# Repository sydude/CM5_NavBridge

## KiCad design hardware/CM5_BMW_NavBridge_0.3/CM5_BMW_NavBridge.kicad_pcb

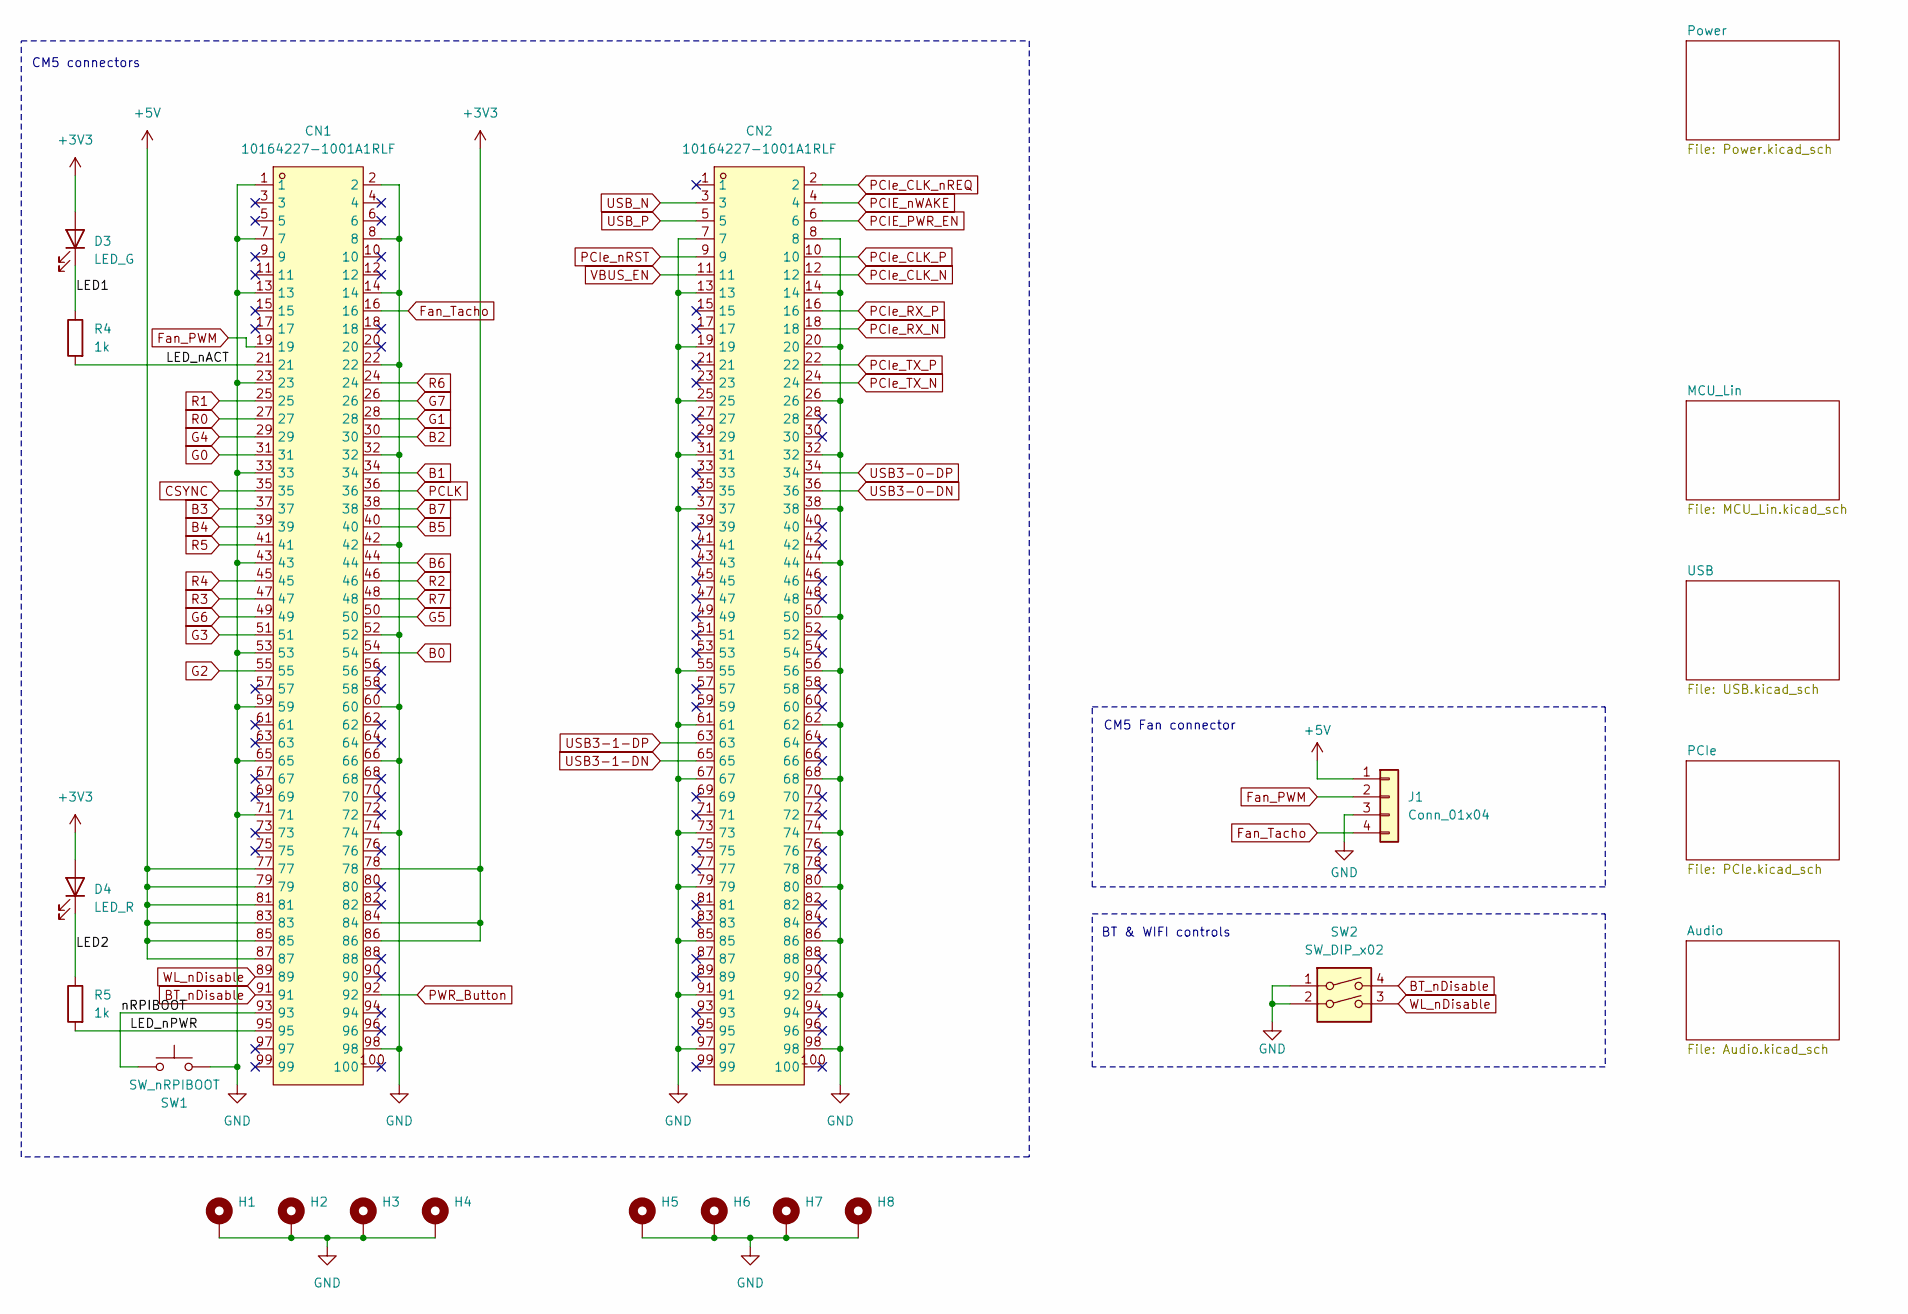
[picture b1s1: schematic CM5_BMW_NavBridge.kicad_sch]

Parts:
CN1, CN2: 10164227-1001A1RLF; CONN-SMD_100P-P0.40_10164227-1001A1RLF; MPN 10164227-1001A1RLF; LCSC Part C6782225
D3: LED_G; LED_0603_1608Metric_Pad1.05x0.95mm_HandSolder
D4: LED_R; LED_0603_1608Metric_Pad1.05x0.95mm_HandSolder
H1, H2, H3, H4, H5, H6, H7, H8: MountingHole_Pad; MountingHole_2.7mm_M2.5_Pad_TopBottom
J1: Conn_01x04; JST_SH_BM04B-SRSS-TB_1x04-1MP_P1.00mm_Vertical
R4, R5: 1k; R_0603_1608Metric_Pad0.98x0.95mm_HandSolder
SW1: SW_nRPIBOOT; SW_SPST_TS-1088-xR025; MPN TS-1088-AR02016; LCSC C720477
SW2: SW_DIP_x02; SW_DIP_SPSTx02_Slide_Copal_CHS-02B_W7.62mm_P1.27mm

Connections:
+3V3: CN1.78, CN1.84, CN1.86, D3.2 (A), D4.2 (A); also elsewhere on the board
+5V: CN1.77, CN1.79, CN1.81, CN1.83, CN1.85, CN1.87, J1.1; also elsewhere on the board
/LED1: D3.1 (K), R4.1
/LED2: D4.1 (K), R5.1
/LED_nACT: CN1.21, R4.2
/LED_nPWR: CN1.95, R5.2
/nRPIBOOT: CN1.93, SW1.1
B0: CN1.54
B1: CN1.34
B2: CN1.30
B3: CN1.37
B4: CN1.39
B5: CN1.40
B6: CN1.44
B7: CN1.38
BT_nDisable: CN1.91, SW2.4
CSYNC: CN1.35
Fan_PWM: CN1.19, J1.2
Fan_Tacho: CN1.16, J1.4
G0: CN1.31
G1: CN1.28
G2: CN1.55
G3: CN1.51
G4: CN1.29
G5: CN1.50
G6: CN1.49
G7: CN1.26
GND: CN1.1, CN1.2, CN1.7, CN1.8, CN1.13, CN1.14, CN1.22, CN1.23, CN1.32, CN1.33, CN1.42, CN1.43, CN1.52, CN1.53, CN1.59, CN1.60, CN1.65, CN1.66, CN1.71, CN1.74, CN1.98, CN2.7, CN2.8, CN2.13, CN2.14, CN2.19, CN2.20, CN2.25, CN2.26, CN2.31, CN2.32, CN2.37, CN2.38, CN2.44, CN2.50, CN2.55, CN2.56, CN2.61, CN2.62, CN2.67, CN2.68, CN2.73, CN2.74, CN2.79, CN2.80, CN2.85, CN2.86, CN2.91, CN2.92, CN2.97, CN2.98, H1.1 (1_1), H2.1 (1_1), H3.1 (1_1), H4.1 (1_1), H5.1 (1_1), H6.1 (1_1), H7.1 (1_1), H8.1 (1_1), J1.3, SW1.2, SW2.1, SW2.2; also elsewhere on the board
PCIE_PWR_EN: CN2.6; also elsewhere on the board
PCIE_nWAKE: CN2.4; also elsewhere on the board
PCIe_CLK_N: CN2.12; also elsewhere on the board
PCIe_CLK_P: CN2.10; also elsewhere on the board
PCIe_CLK_nREQ: CN2.2; also elsewhere on the board
PCIe_RX_N: CN2.18; also elsewhere on the board
PCIe_RX_P: CN2.16; also elsewhere on the board
PCIe_TX_N: CN2.24; also elsewhere on the board
PCIe_TX_P: CN2.22; also elsewhere on the board
PCIe_nRST: CN2.9; also elsewhere on the board
PCLK: CN1.36
PWR_Button: CN1.92; also elsewhere on the board
R0: CN1.27
R1: CN1.25
R2: CN1.46
R3: CN1.47
R4: CN1.45
R5: CN1.41
R6: CN1.24
R7: CN1.48
USB3-0-DN: CN2.36; also elsewhere on the board
USB3-0-DP: CN2.34; also elsewhere on the board
USB3-1-DN: CN2.65; also elsewhere on the board
USB3-1-DP: CN2.63; also elsewhere on the board
USB_N: CN2.3; also elsewhere on the board
USB_P: CN2.5; also elsewhere on the board
VBUS_EN: CN2.11; also elsewhere on the board
WL_nDisable: CN1.89, SW2.3

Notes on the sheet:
CM5 Fan connector
CM5 connectors
BT & WIFI controls

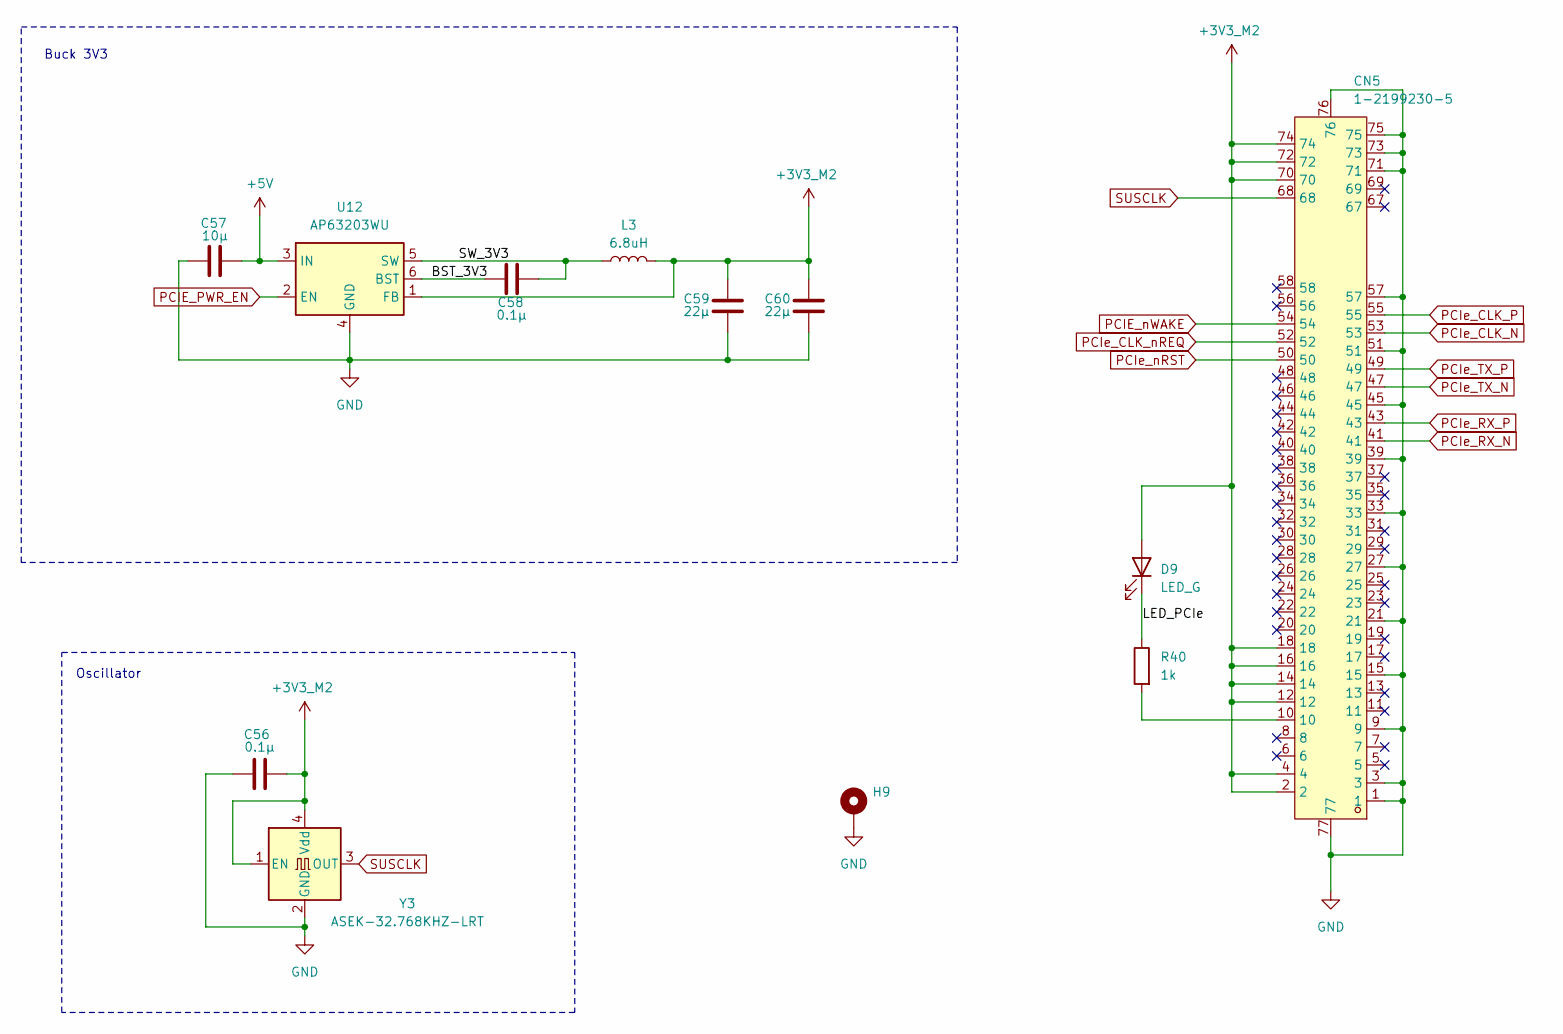
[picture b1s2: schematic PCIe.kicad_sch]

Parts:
C56, C58: 0.1µ; C_0603_1608Metric_Pad1.08x0.95mm_HandSolder; LCSC C1591
C57: 10µ; C_0805_2012Metric_Pad1.18x1.45mm_HandSolder; LCSC C95841
C59, C60: 22µ; C_1206_3216Metric_Pad1.33x1.80mm_HandSolder; LCSC C87996
CN5: 1-2199230-5; PCIE-SMD_75P-P0.50_1-2199230-5; LCSC Part C590854
D9: LED_G; LED_0603_1608Metric_Pad1.05x0.95mm_HandSolder
H9: MountingHole_Pad; MountingHole_2.2mm_M2_DIN965_Pad_TopBottom
L3: 6.8uH; L_Sunlord_MWSA0518S; LCSC C2928918
R40: 1k; R_0603_1608Metric_Pad0.98x0.95mm_HandSolder
U12: AP63203WU; TSOT-23-6; LCSC C780769
Y3: ASEK-32.768KHZ-LRT; Oscillator_SMD_Abracon_ASE-4Pin_3.2x2.5mm_HandSoldering; LCSC C2650753

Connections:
+3V3_M2: C56.1, C59.1, C60.1, CN5.2, CN5.4, CN5.12, CN5.14, CN5.16, CN5.18, CN5.70, CN5.72, CN5.74, D9.2 (A), L3.2, U12.1 (FB), Y3.1 (EN), Y3.4 (Vdd)
+5V: C57.2, U12.3 (IN); also elsewhere on the board
/PCIe/BST_3V3: C58.2, U12.6 (BST)
/PCIe/LED_PCIe: D9.1 (K), R40.1
/PCIe/SW_3V3: C58.1, L3.1, U12.5 (SW)
GND: C56.2, C57.1, C59.2, C60.2, CN5.1, CN5.3, CN5.9, CN5.15, CN5.21, CN5.27, CN5.33, CN5.39, CN5.45, CN5.51, CN5.57, CN5.71, CN5.73, CN5.75, CN5.76, CN5.77, H9.1 (1_1), U12.4 (GND), Y3.2 (GND); also elsewhere on the board
unnamed: CN5.10, R40.2
PCIE_PWR_EN: U12.2 (EN); also elsewhere on the board
PCIE_nWAKE: CN5.54; also elsewhere on the board
PCIe_CLK_N: CN5.53; also elsewhere on the board
PCIe_CLK_P: CN5.55; also elsewhere on the board
PCIe_CLK_nREQ: CN5.52; also elsewhere on the board
PCIe_RX_N: CN5.41; also elsewhere on the board
PCIe_RX_P: CN5.43; also elsewhere on the board
PCIe_TX_N: CN5.47; also elsewhere on the board
PCIe_TX_P: CN5.49; also elsewhere on the board
PCIe_nRST: CN5.50; also elsewhere on the board
SUSCLK: CN5.68, Y3.3 (OUT)

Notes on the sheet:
Buck 3V3
Oscillator

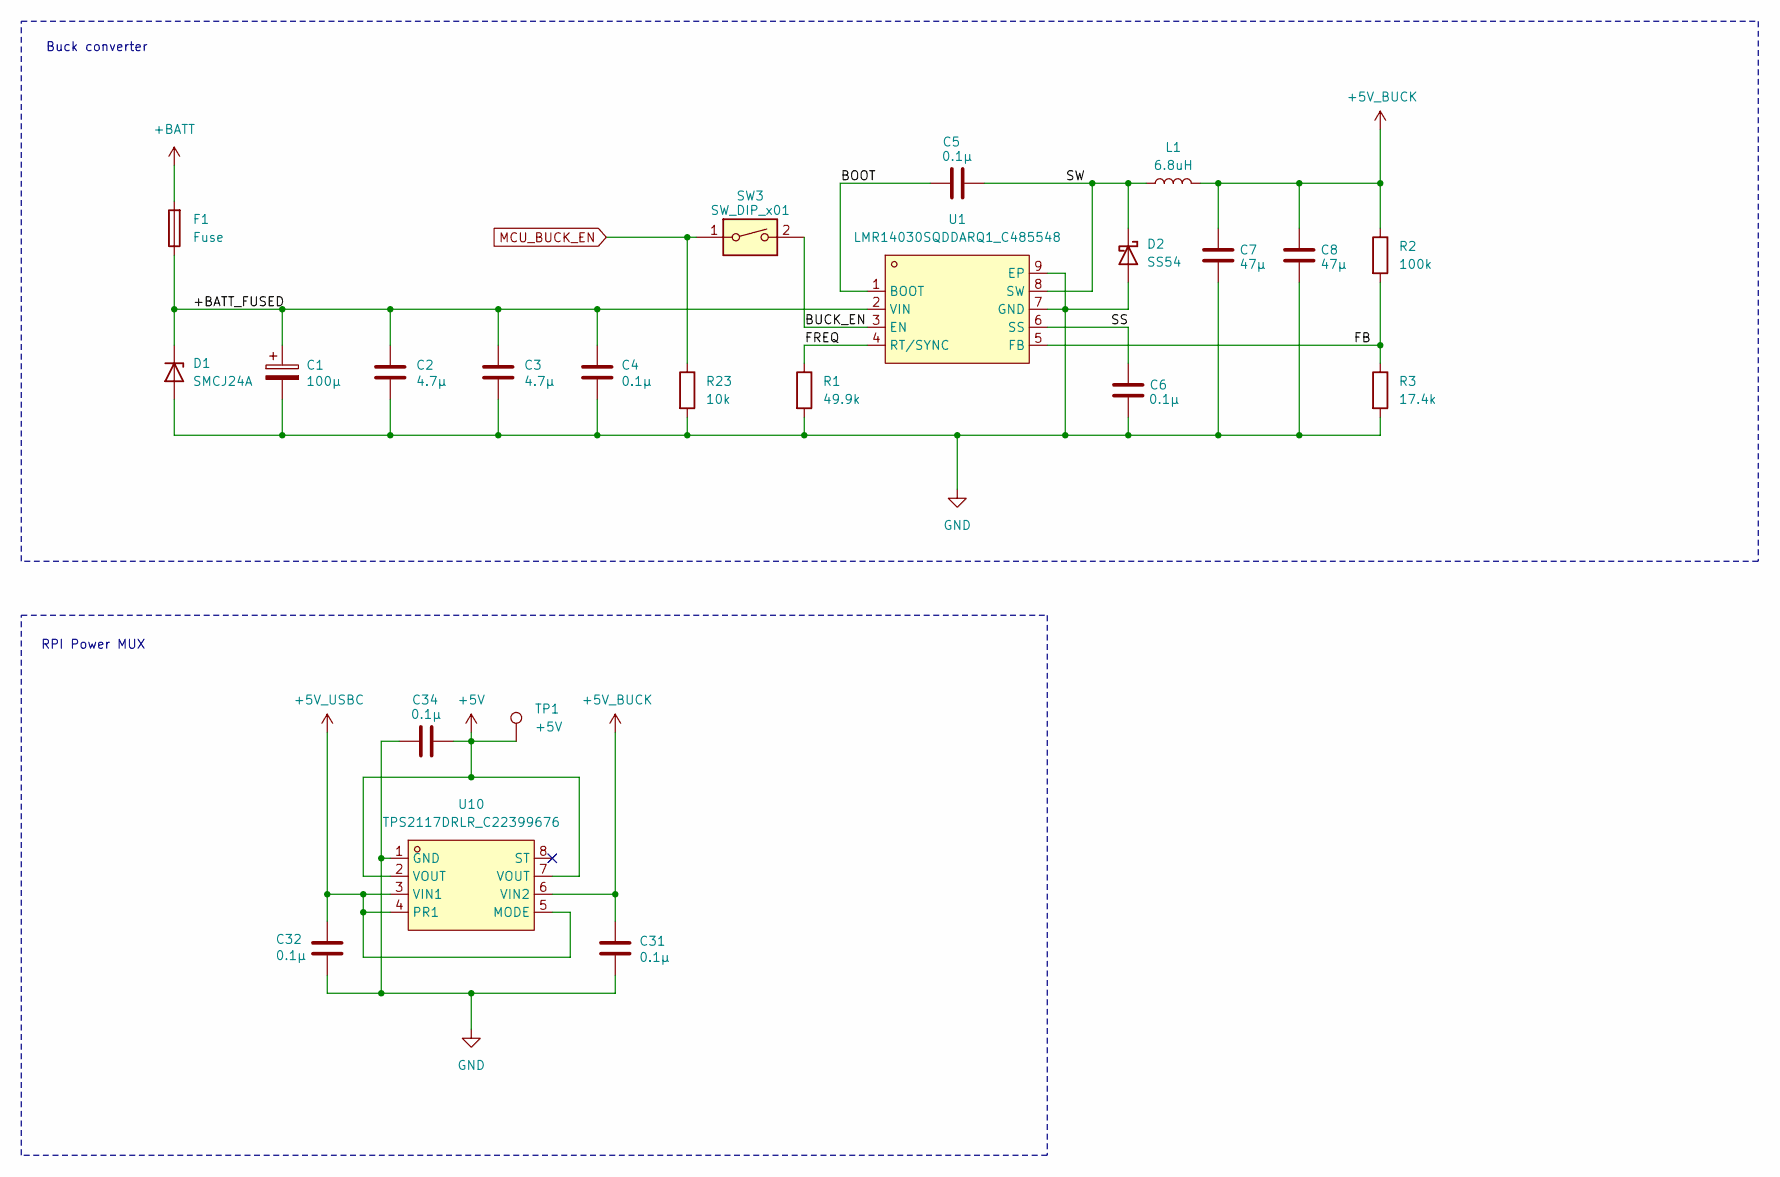
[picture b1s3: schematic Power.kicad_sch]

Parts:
C1: 100µ; CP_Elec_6.3x5.8; LCSC C128464
C2, C3: 4.7µ; C_1206_3216Metric_Pad1.33x1.80mm_HandSolder; LCSC C51205
C4, C5, C6, C31, C32, C34: 0.1µ; C_0603_1608Metric_Pad1.08x0.95mm_HandSolder; LCSC C1591
C7, C8: 47µ; C_1210_3225Metric_Pad1.33x2.70mm_HandSolder; LCSC C2932477
D1: SMCJ24A; D_SMC; LCSC C224045
D2: SS54; D_SMA; LCSC C22452
F1: Fuse; Fuseholder_Littelfuse_Nano2_154x; LCSC C108518
L1: 6.8uH; L_Sunlord_MWSA1003S; LCSC C2453947
R1: 49.9k; R_0603_1608Metric_Pad0.98x0.95mm_HandSolder
R2: 100k; R_0603_1608Metric_Pad0.98x0.95mm_HandSolder
R3: 17.4k; R_0603_1608Metric_Pad0.98x0.95mm_HandSolder
R23: 10k; R_0603_1608Metric_Pad0.98x0.95mm_HandSolder
SW3: SW_DIP_x01; SW_DIP_SPSTx01_Slide_Copal_CHS-01B_W7.62mm_P1.27mm
TP1: +5V; TestPoint_Pad_1.0x1.0mm
U1: LMR14030SQDDARQ1_C485548; SOPOWERPAD-8_L4.9-W3.9-P1.27-LS6.0-BL-EP; LCSC Part C485548
U10: TPS2117DRLR_C22399676; SOT-583-8_L2.1-W1.2-P0.50-LS1.6-BL; LCSC Part C22399676

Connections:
+5V: C34.2, TP1.1 (1_1), U10.2 (VOUT), U10.7 (VOUT); also elsewhere on the board
+5V_BUCK: C7.1, C8.1, C31.1, L1.2, R2.1, U10.6 (VIN2); also elsewhere on the board
+5V_USBC: C32.1, U10.3 (VIN1), U10.4 (PR1), U10.5 (MODE); also elsewhere on the board
+BATT: F1.2
/Power/+BATT_FUSED: C1.1, C2.1, C3.1, C4.1, D1.1 (K), F1.1, U1.2 (VIN)
/Power/BOOT: C5.1, U1.1 (BOOT)
/Power/BUCK_EN: SW3.2, U1.3 (EN)
/Power/FB: R2.2, R3.1, U1.5 (FB)
/Power/FREQ: R1.1, U1.4 (RT/SYNC)
/Power/SS: C6.1, U1.6 (SS)
/Power/SW: C5.2, D2.1 (K), L1.1, U1.8 (SW)
GND: C1.2, C2.2, C3.2, C4.2, C6.2, C7.2, C8.2, C31.2, C32.2, C34.1, D1.2 (A), D2.2 (A), R1.2, R3.2, R23.2, U1.7 (GND), U1.9 (EP), U10.1 (GND); also elsewhere on the board
MCU_BUCK_EN: R23.1, SW3.1; also elsewhere on the board

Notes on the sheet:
Buck converter
RPI Power MUX

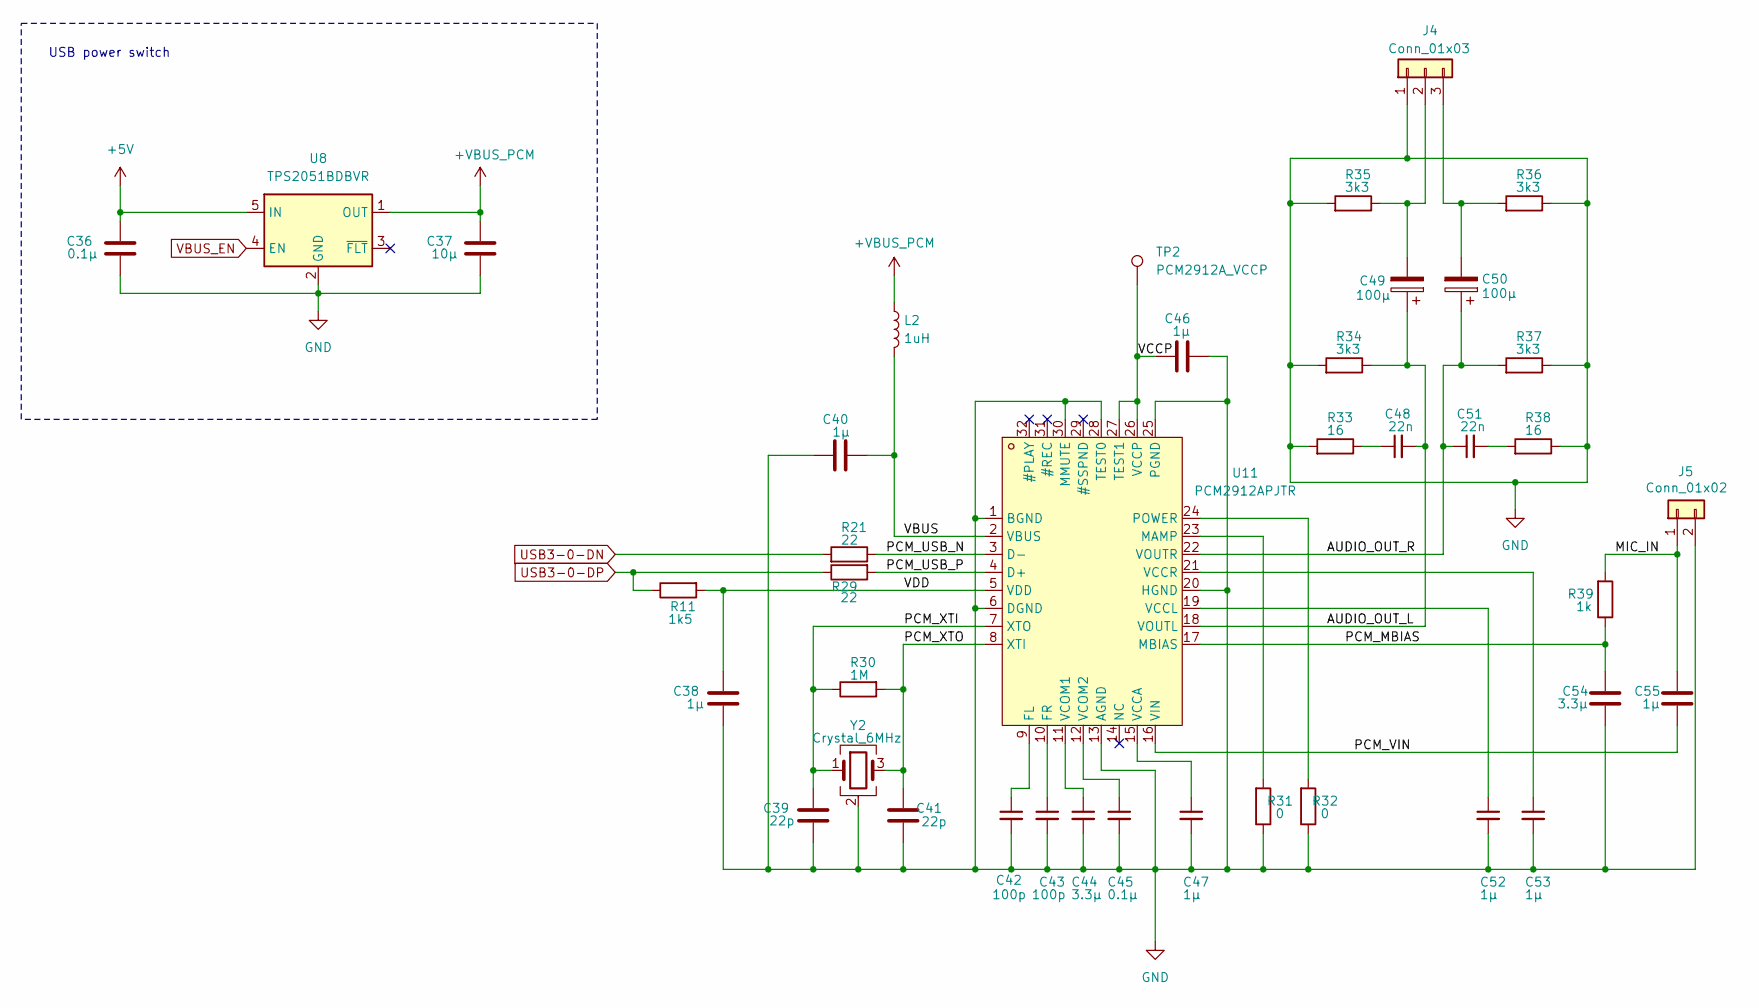
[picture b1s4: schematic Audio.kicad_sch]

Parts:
C36, C45: 0.1µ; C_0603_1608Metric_Pad1.08x0.95mm_HandSolder; LCSC C1591
C37: 10µ; C_0805_2012Metric_Pad1.18x1.45mm_HandSolder; LCSC C95841
C38, C40, C46, C47, C52, C53, C55: 1µ; C_0603_1608Metric_Pad1.08x0.95mm_HandSolder; LCSC C29936
C39, C41: 22p; C_0603_1608Metric_Pad1.08x0.95mm_HandSolder; LCSC C1653
C42, C43: 100p; C_0603_1608Metric_Pad1.08x0.95mm_HandSolder; LCSC C14858
C44, C54: 3.3µ; C_0603_1608Metric_Pad1.08x0.95mm_HandSolder; LCSC C51412
C48, C51: 22n; C_0603_1608Metric_Pad1.08x0.95mm_HandSolder; LCSC C21122
C49, C50: 100µ; CP_EIA-3528-21_Kemet-B_HandSolder; LCSC C79109
J4: Conn_01x03; JST_GH_SM03B-GHS-TB_1x03-1MP_P1.25mm_Horizontal
J5: Conn_01x02; JST_GH_SM02B-GHS-TB_1x02-1MP_P1.25mm_Horizontal
L2: 1uH; L_1008_2520Metric_Pad1.43x2.20mm_HandSolder; LCSC C435392
R11: 1k5; R_0603_1608Metric_Pad0.98x0.95mm_HandSolder
R21, R29: 22; R_0603_1608Metric_Pad0.98x0.95mm_HandSolder
R30: 1M; R_0603_1608Metric_Pad0.98x0.95mm_HandSolder
R31, R32: 0; R_0603_1608Metric_Pad0.98x0.95mm_HandSolder
R33, R38: 16; R_0603_1608Metric_Pad0.98x0.95mm_HandSolder
R34, R35, R36, R37: 3k3; R_0603_1608Metric_Pad0.98x0.95mm_HandSolder
R39: 1k; R_0603_1608Metric_Pad0.98x0.95mm_HandSolder
TP2: PCM2912A_VCCP; TestPoint_Pad_1.0x1.0mm
U8: TPS2051BDBVR; SOT-23-5; LCSC C24593
U11: PCM2912APJTR; TQFP-32_L7.0-W7.0-P0.80-LS9.0-TL; MPN PCM2912APJTR; LCSC Part C475497
Y2: Crystal_6MHz; Crystal_SMD_FOX_FQ7050-4Pin_7.0x5.0mm; MPN ABMM-6.000MHZ-B2-T; LCSC C179631

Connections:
+5V: C36.2, U8.5 (IN); also elsewhere on the board
+VBUS_PCM: C37.2, L2.1, U8.1 (OUT)
/Audio/AUDIO_OUT_L: C48.2, C49.1, R34.1, U11.18 (VOUTL)
/Audio/AUDIO_OUT_R: C50.1, C51.1, R37.2, U11.22 (VOUTR)
/Audio/MIC_IN: C55.1, J5.1, R39.2
/Audio/PCM_MBIAS: C54.1, R39.1, U11.17 (MBIAS)
/Audio/PCM_USB_N: R21.1, U11.3 (D-)
/Audio/PCM_USB_P: R29.2, U11.4 (D+)
/Audio/PCM_VIN: C55.2, U11.16 (VIN)
/Audio/PCM_XTI: C39.2, R30.1, U11.7 (XTO), Y2.1
/Audio/PCM_XTO: C41.2, R30.2, U11.8 (XTI), Y2.3
/Audio/VBUS: C40.1, L2.2, U11.2 (VBUS)
/Audio/VCCP: C46.1, TP2.1 (1_1), U11.26 (VCCP), U11.27 (TEST1)
/Audio/VDD: C38.2, R11.2, U11.5 (VDD)
GND: C36.1, C37.1, C38.1, C39.1, C40.2, C41.1, C42.2, C43.2, C44.2, C45.2, C46.2, C47.2, C52.2, C53.2, C54.2, J4.1, J5.2, R31.1, R32.1, R33.2, R34.2, R35.2, R36.1, R37.1, R38.1, U8.2 (GND), U11.1 (BGND), U11.6 (DGND), U11.13 (AGND), U11.20 (HGND), U11.25 (PGND), U11.28 (TEST0), U11.30 (MMUTE), Y2.2 (G), Y2.4 (G); also elsewhere on the board
unnamed: C48.1, R33.1
unnamed: C51.2, R38.2
unnamed: C49.2, J4.2, R35.1
unnamed: C50.2, J4.3, R36.2
unnamed: C42.1, U11.9 (FL)
unnamed: C43.1, U11.10 (FR)
unnamed: R31.2, U11.23 (MAMP)
unnamed: R32.2, U11.24 (POWER)
unnamed: C47.1, U11.15 (VCCA)
unnamed: C52.1, U11.19 (VCCL)
unnamed: C53.1, U11.21 (VCCR)
unnamed: C44.1, U11.11 (VCOM1)
unnamed: C45.1, U11.12 (VCOM2)
USB3-0-DN: R21.2; also elsewhere on the board
USB3-0-DP: R11.1, R29.1; also elsewhere on the board
VBUS_EN: U8.4 (EN); also elsewhere on the board

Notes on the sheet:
USB power switch

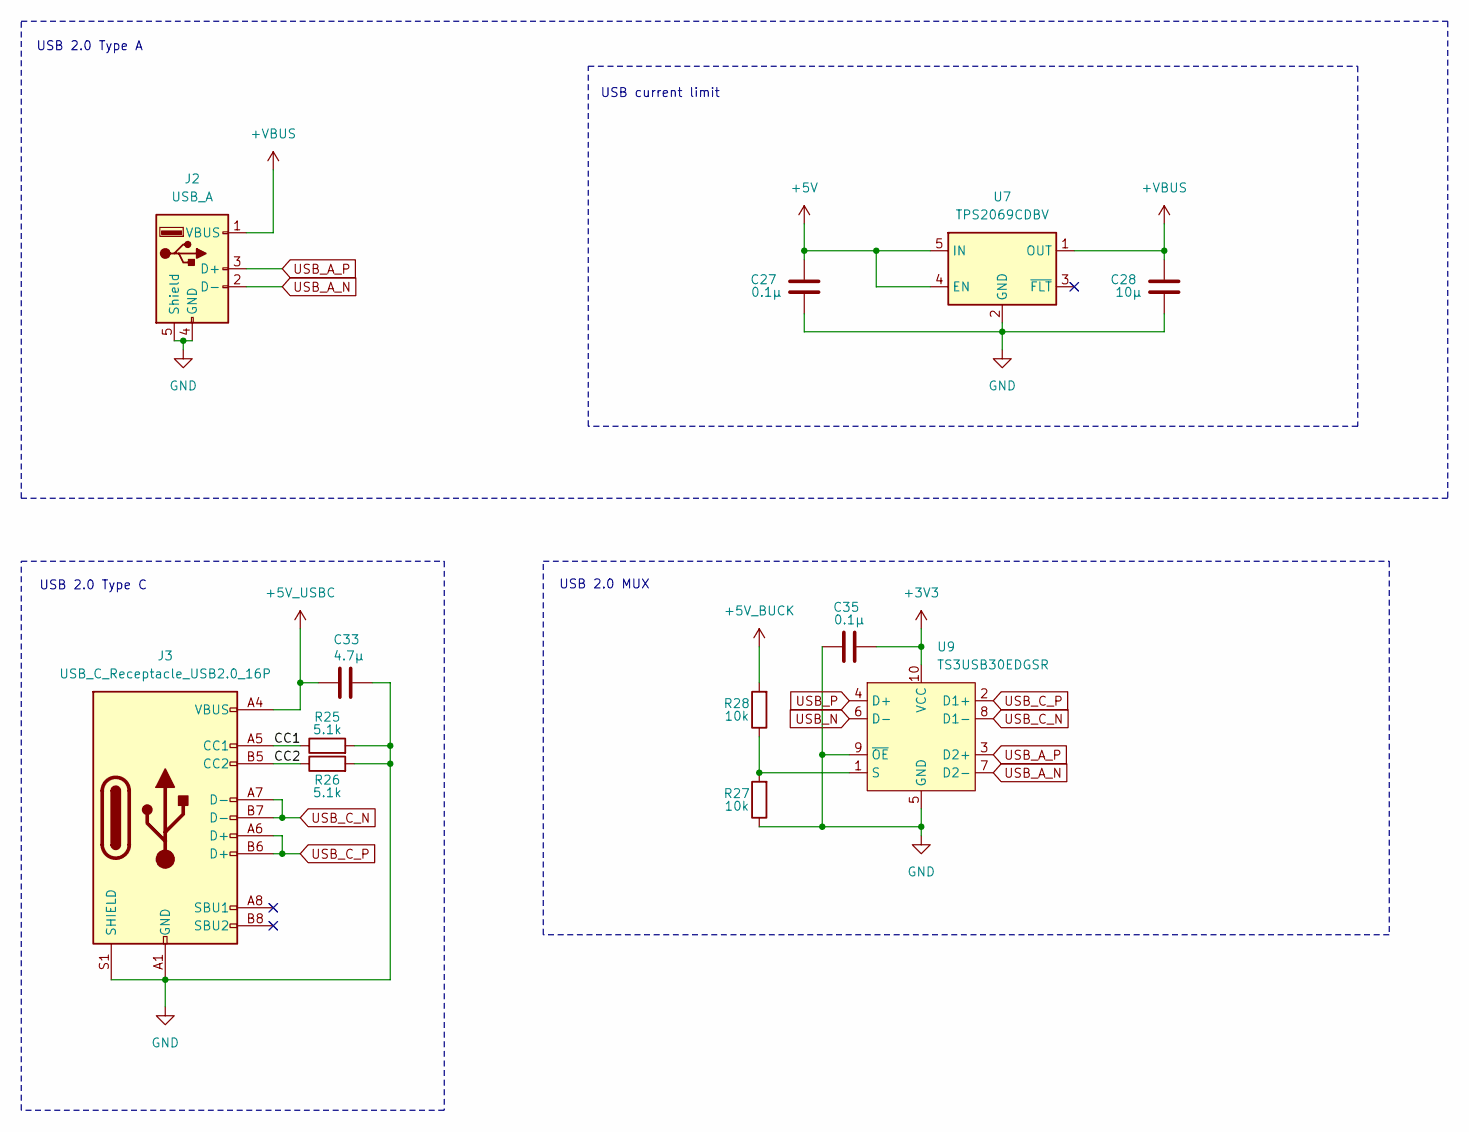
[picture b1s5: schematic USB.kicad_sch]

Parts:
C27, C35: 0.1µ; C_0603_1608Metric_Pad1.08x0.95mm_HandSolder; LCSC C1591
C28: 10µ; C_0805_2012Metric_Pad1.18x1.45mm_HandSolder; LCSC C95841
C33: 4.7µ; C_1206_3216Metric_Pad1.33x1.80mm_HandSolder; LCSC C51205
J2: USB_A; USB_A_Receptacle_GCT_USB1046
J3: USB_C_Receptacle_USB2.0_16P; USB_C_Receptacle_G-Switch_GT-USB-7010ASV; LCSC C2988369
R25, R26: 5.1k; R_0603_1608Metric_Pad0.98x0.95mm_HandSolder
R27, R28: 10k; R_0603_1608Metric_Pad0.98x0.95mm_HandSolder
U7: TPS2069CDBV; SOT-23-5; MPN TPS2069CDBVR
U9: TS3USB30EDGSR; VSSOP-10_3x3mm_P0.5mm

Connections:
+3V3: C35.1, U9.10 (VCC); also elsewhere on the board
+5V: C27.2, U7.4 (EN), U7.5 (IN); also elsewhere on the board
+5V_BUCK: R28.2; also elsewhere on the board
+5V_USBC: C33.1, J3.A4 (VBUS), J3.A9 (VBUS), J3.B4 (VBUS), J3.B9 (VBUS); also elsewhere on the board
+VBUS: C28.2, J2.1 (VBUS), U7.1 (OUT)
/USB/CC1: J3.A5 (CC1), R25.1
/USB/CC2: J3.B5 (CC2), R26.1
GND: C27.1, C28.1, C33.2, C35.2, J2.4 (GND), J2.5 (Shield), J3.A1 (GND), J3.A12 (GND), J3.B1 (GND), J3.B12 (GND), J3.S1 (SHIELD), R25.2, R26.2, R27.1, U7.2 (GND), U9.5 (GND), U9.9 (~OE); also elsewhere on the board
unnamed: R27.2, R28.1, U9.1 (S)
USB_A_N: J2.2 (D-), U9.7 (D2-)
USB_A_P: J2.3 (D+), U9.3 (D2+)
USB_C_N: J3.A7 (D-), J3.B7 (D-), U9.8 (D1-)
USB_C_P: J3.A6 (D+), J3.B6 (D+), U9.2 (D1+)
USB_N: U9.6 (D-); also elsewhere on the board
USB_P: U9.4 (D+); also elsewhere on the board

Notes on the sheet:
USB current limit
USB 2.0 Type A
USB 2.0 MUX
USB 2.0 Type C

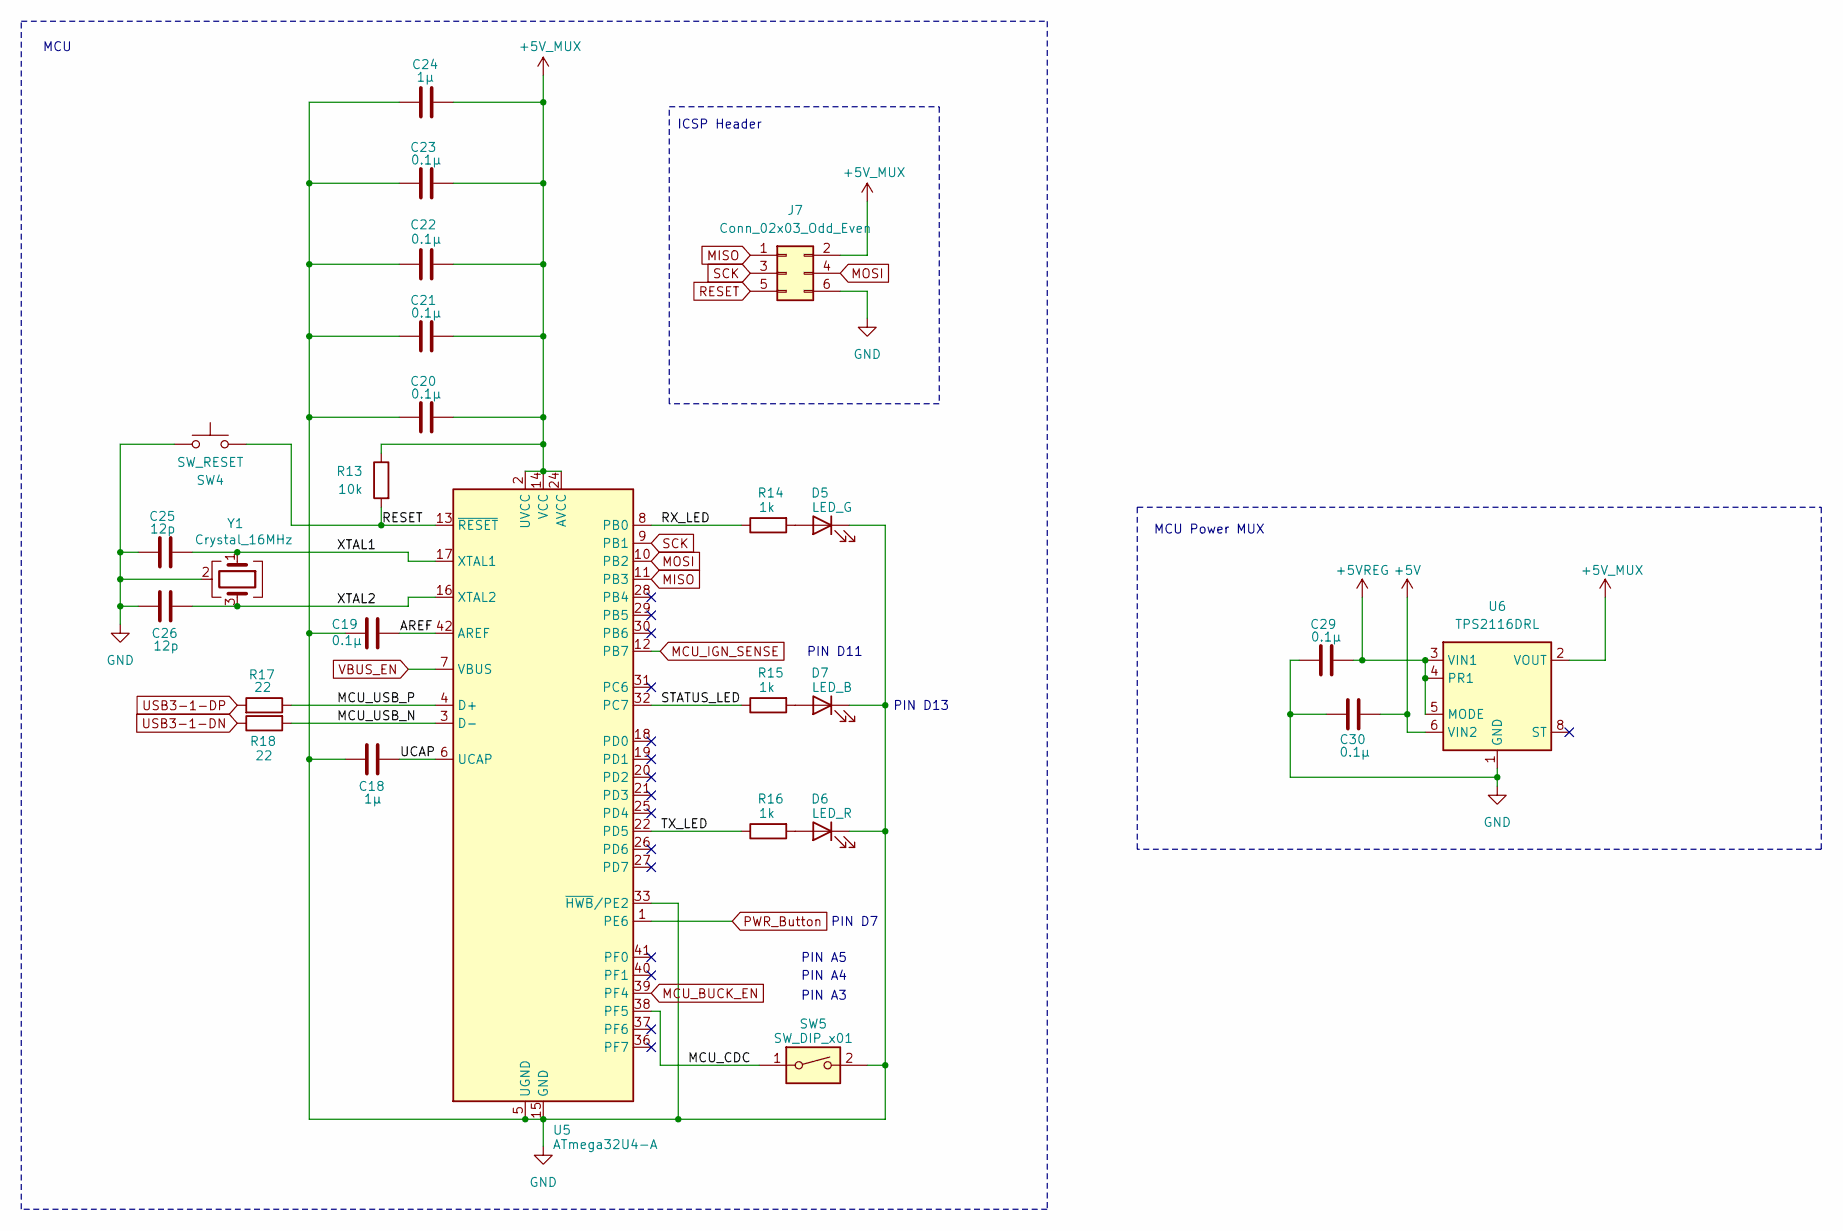
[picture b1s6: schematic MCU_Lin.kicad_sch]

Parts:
C18, C24: 1µ; C_0603_1608Metric_Pad1.08x0.95mm_HandSolder; LCSC C1591
C19, C20, C21, C22, C23, C29, C30: 0.1µ; C_0603_1608Metric_Pad1.08x0.95mm_HandSolder; LCSC C1591
C25, C26: 12p; C_0603_1608Metric_Pad1.08x0.95mm_HandSolder; LCSC C38523
D5: LED_G; LED_0603_1608Metric_Pad1.05x0.95mm_HandSolder
D6: LED_R; LED_0603_1608Metric_Pad1.05x0.95mm_HandSolder
D7: LED_B; LED_0603_1608Metric_Pad1.05x0.95mm_HandSolder
J7: Conn_02x03_Odd_Even; PinHeader_2x03_P2.54mm_Vertical
R13: 10k; R_0603_1608Metric_Pad0.98x0.95mm_HandSolder
R14, R15, R16: 1k; R_0603_1608Metric_Pad0.98x0.95mm_HandSolder
R17, R18: 22; R_0603_1608Metric_Pad0.98x0.95mm_HandSolder
SW4: SW_RESET; SW_SPST_TS-1088-xR025; MPN TS-1088-AR02016; LCSC C720477
SW5: SW_DIP_x01; SW_DIP_SPSTx01_Slide_Copal_CHS-01B_W7.62mm_P1.27mm
U5: ATmega32U4-A; TQFP-44_10x10mm_P0.8mm; MPN ATMEGA32U4-AU
U6: TPS2116DRL; SOT-583-8
Y1: Crystal_16MHz; Crystal_SMD_3225-4Pin_3.2x2.5mm; MPN NX3225SA-16MHz-STD-CSR-6; LCSC C880097

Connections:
+5V: C30.1, U6.6 (VIN2); also elsewhere on the board
+5VREG: C29.2, U6.3 (VIN1), U6.4 (PR1), U6.5 (MODE)
+5V_MUX: C20.2, C21.2, C22.2, C23.2, C24.2, J7.2, R13.1, U5.2 (UVCC), U5.14 (VCC), U5.24 (AVCC), U5.34 (VCC), U5.44 (AVCC), U6.2 (VOUT), U6.7 (VOUT)
/MCU_Lin/AREF: C19.1, U5.42 (AREF)
/MCU_Lin/MCU_CDC: SW5.1, U5.38 (PF5)
/MCU_Lin/MCU_USB_N: R18.2, U5.3 (D-)
/MCU_Lin/MCU_USB_P: R17.1, U5.4 (D+)
/MCU_Lin/RX_LED: R14.1, U5.8 (PB0)
/MCU_Lin/STATUS_LED: R15.1, U5.32 (PC7)
/MCU_Lin/TX_LED: R16.1, U5.22 (PD5)
/MCU_Lin/UCAP: C18.1, U5.6 (UCAP)
/MCU_Lin/XTAL1: C25.2, U5.17 (XTAL1), Y1.1
/MCU_Lin/XTAL2: C26.1, U5.16 (XTAL2), Y1.3
GND: C18.2, C19.2, C20.1, C21.1, C22.1, C23.1, C24.1, C25.1, C26.2, C29.1, C30.2, D5.1 (K), D6.1 (K), D7.1 (K), J7.6, SW4.1, SW5.2, U5.5 (UGND), U5.15 (GND), U5.23 (GND), U5.33 (~HWB/PE2), U5.35 (GND), U5.43 (GND), U6.1 (GND), Y1.2 (G), Y1.4 (G); also elsewhere on the board
MCU_BUCK_EN: U5.39 (PF4); also elsewhere on the board
MCU_IGN_SENSE: U5.12 (PB7)
MISO: J7.1, U5.11 (PB3)
MOSI: J7.4, U5.10 (PB2)
unnamed: D5.2 (A), R14.2
unnamed: D6.2 (A), R16.2
unnamed: D7.2 (A), R15.2
PWR_Button: U5.1 (PE6); also elsewhere on the board
RESET: J7.5, R13.2, SW4.2, U5.13 (~RESET)
SCK: J7.3, U5.9 (PB1)
USB3-1-DN: R18.1; also elsewhere on the board
USB3-1-DP: R17.2; also elsewhere on the board
VBUS_EN: U5.7 (VBUS); also elsewhere on the board

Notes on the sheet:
PIN A3
ICSP Header
MCU
MCU Power MUX
PIN A4
PIN D7
PIN D13
PIN A5
PIN D11

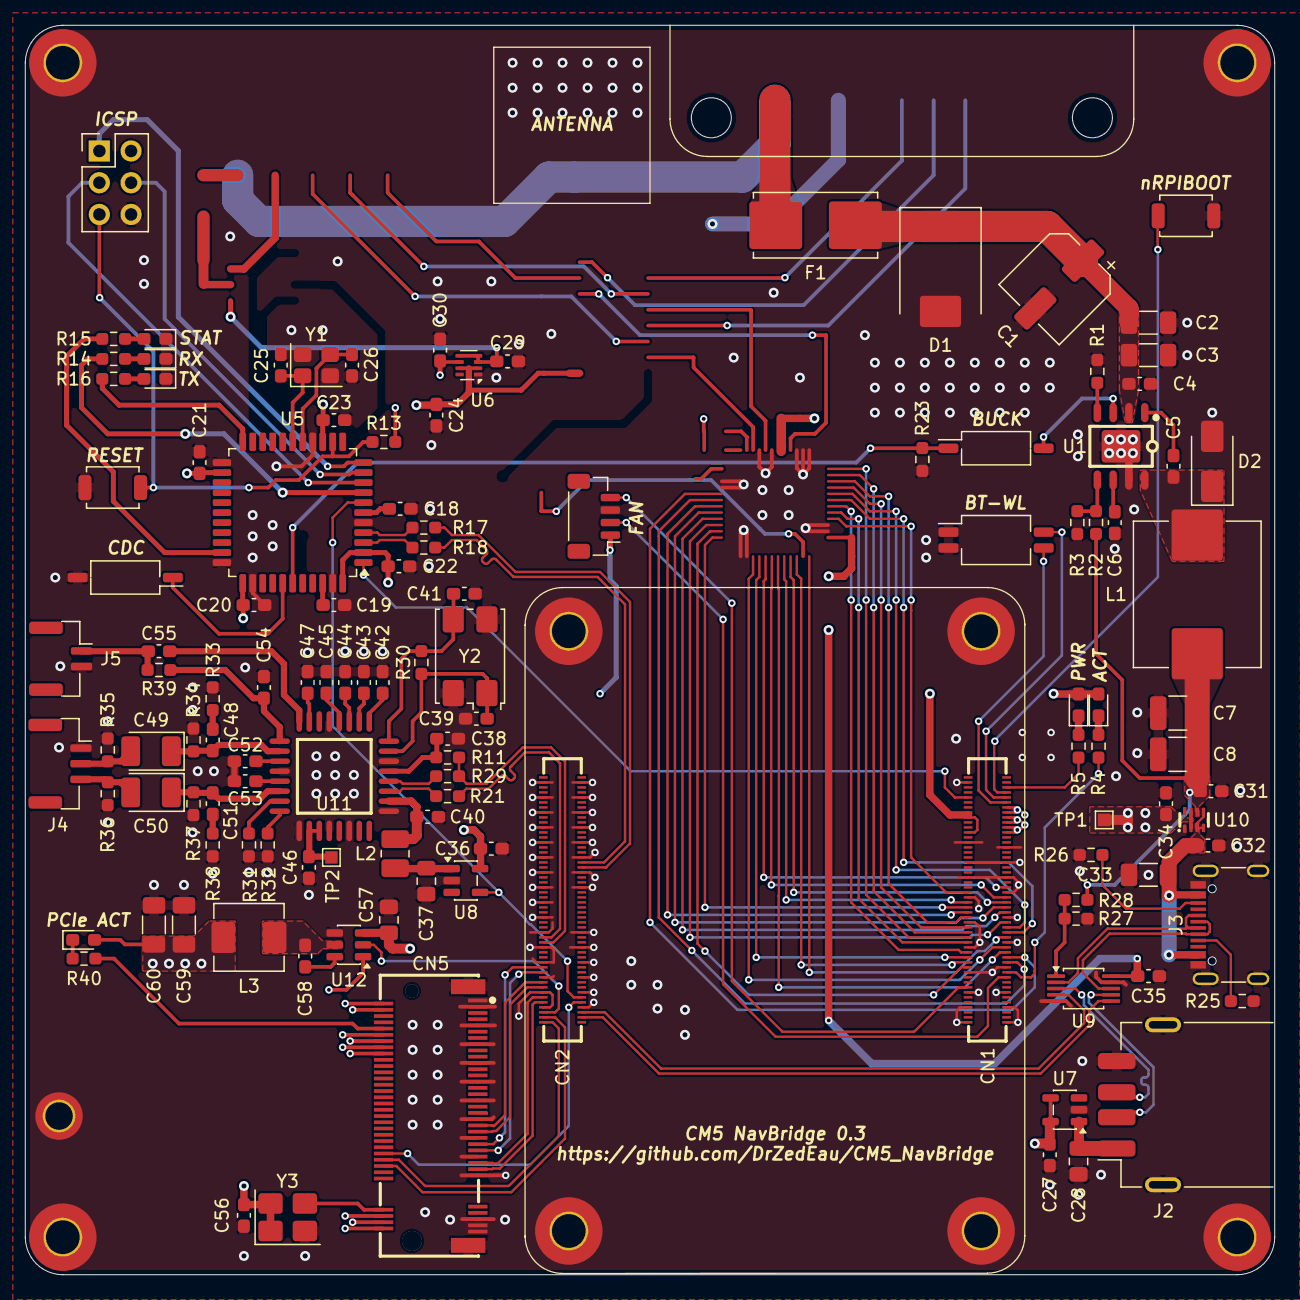
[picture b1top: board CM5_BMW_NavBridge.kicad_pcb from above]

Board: 4 copper layers, 100.0 x 100.0 mm, 130 parts (0 on the bottom side), 99 nets.
